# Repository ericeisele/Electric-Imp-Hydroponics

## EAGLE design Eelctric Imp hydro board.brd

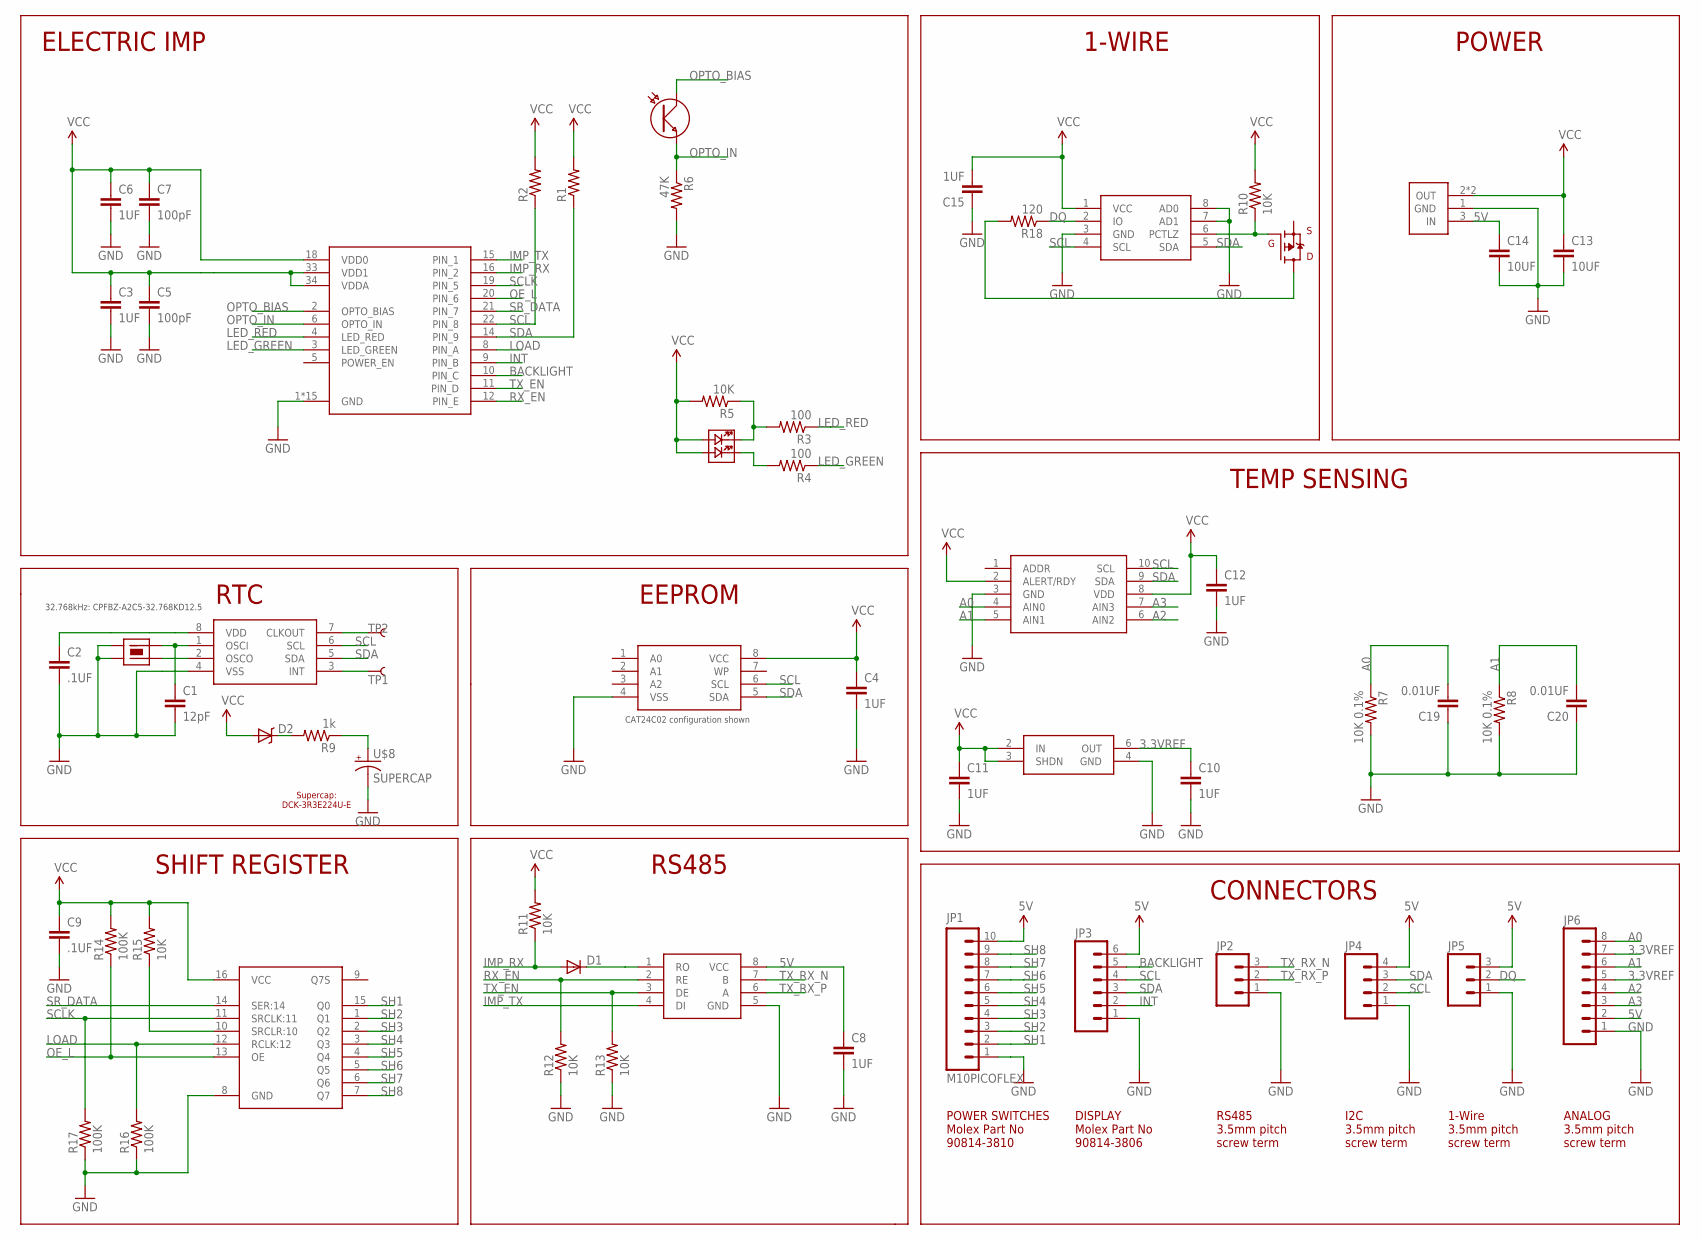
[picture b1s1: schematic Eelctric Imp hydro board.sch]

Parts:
C1: 12pF; 0805
C2, C9: .1UF; 0805
C3, C4, C6, C8, C10, C11, C12, C15: 1UF; 0805
C5, C7: 100pF; 0805
C13, C14: 10UF; 0805
C19, C20: 0.01UF; 0805
D1: DIODESOD; SOD-323
D2: DIODE-SCHOTTKY_; SMA-DIODE
JP1: M10PICOFLEX; CONNECTOR_MOLEX_PICOFLEX_10
JP2, JP5: M03SCREW_LOCK; SCREWTERMINAL-3.5MM-3_LOCK.007S
JP3: M06PICOFLEX; CONNECTOR_MOLEX_PICOFLEX_6
JP4: M04SCREW_LOCK; SCREWTERMINAL-3.5MM-4_LOCK
JP6: M083.5MM-8; SCREWTERMINAL-3.5MM-8
R1, R2: RESISTOR0805-RES; 0805
R3, R4: 100; 0805
R5, R10, R11, R12, R13, R15: 10K; 0805
R6: 47K; 0805
R7, R8: 10K 0.1%; 0805
R9: 1k; 0805
R14, R16, R17: 100K; 0805
R18: 120; 0805
TP1, TP2: TEST-POINT3; PAD.03X.03
U$1: RTC_PCF8563; SOIC8
U$2: CRYSTAL_4PIN232.768KHZ_ABS25; CRYSTAL_ABS25
U$3: EEPROM_CAT24CXX; SOIC8
U$4: RF_MODULE_IMP002
U$5: LED_BI_COLOR_4PIN; LED_LITEON_BICOLOR_TOP
U$6: PHOTOTRANSISTOR0805; 0805POL
U$8: SUPERCAP; SUPERCAP_ELENA_DCK_3R3E224U-E
U$9: DS2482-100; SO08
U$10: SHIFT_NXP_74HC595; SO-16
U$11: V_REG_LDO_3SOT-223-4_TI_TLV1117LV; SOT223
U$12: TRANSCEIVER_ST485; SOIC8
U$13: ADC_ADS1115; MSOP10
U$15: VREF_LT1461; SOIC8
U$16: MOSFET-P-CHANNELBSS84; SOT23

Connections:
3.3VREF: C10.1, JP6.5, JP6.7, U$15.6 (OUT)
5V: C8.1, C14.1, JP1.10, JP3.6, JP4.4, JP5.3, JP6.2, U$11.3 (IN), U$12.8 (VCC)
A0: C19.2, JP6.8, R7.1, U$13.4 (AIN0)
A1: C20.2, JP6.6, R8.1, U$13.5 (AIN1)
A2: JP6.4, U$13.6 (AIN2)
A3: JP6.3, U$13.7 (AIN3)
BACKLIGHT: JP3.5, U$4.10 (PIN_C)
DQ: JP5.2, R18.1, U$9.2 (IO)
GND: C1.2, C2.2, C3.2, C4.2, C5.2, C6.2, C7.2, C8.2, C9.2, C10.2, C11.2, C12.2, C13.2, C14.2, C15.1, C19.1, C20.1, JP1.1, JP2.1, JP3.1, JP4.1, JP5.1, JP6.1, R6.2, R7.2, R8.2, R12.1, R13.1, R16.1, R17.1, U$1.4 (VSS), U$2.2 (CASE2), U$2.3 (CASE1), U$3.4 (VSS), U$4.1 (GND), U$4.7 (GND), U$4.13 (GND), U$4.17 (GND), U$4.23 (GND), U$4.24 (GND), U$4.25 (GND), U$4.26 (GND), U$4.27 (GND), U$4.28 (GND), U$4.29 (GND), U$4.30 (GND), U$4.31 (GND), U$4.32 (GND), U$4.35 (GND), U$8.-, U$9.3 (GND), U$9.7 (AD1), U$9.8 (AD0), U$10.8 (GND), U$11.1 (GND), U$12.5 (GND), U$13.3 (GND), U$15.4 (GND)
IMP_RX: D1.2 (A), R11.1, U$4.16 (PIN_2)
IMP_TX: U$4.15 (PIN_1), U$12.4 (DI)
INT: JP3.2, U$4.9 (PIN_B)
LED_GREEN: R4.1, U$4.3 (LED_GREEN)
LED_RED: R3.1, U$4.4 (LED_RED)
LOAD: R16.2, U$4.8 (PIN_A), U$10.12 (RCLK:12)
unnamed: R18.2, U$16.3 (D)
unnamed: C1.1, U$1.1 (OSCI), U$2.1
unnamed: U$1.2 (OSCO), U$2.4
unnamed: TP1.P$1, U$1.3 (INT)
unnamed: TP2.P$1, U$1.7 (CLKOUT)
unnamed: D2.C, R9.2
unnamed: R3.2, R5.1, U$5.LONG-
unnamed: R15.1, U$10.10 (SRCLR:10)
unnamed: R4.2, U$5.SHORT-
unnamed: R10.1, U$9.6 (PCTLZ), U$16.1 (G)
OE_L: R14.1, U$4.20 (PIN_6), U$10.13 (OE)
OPTO_BIAS: U$4.2 (OPTO_BIAS), U$6.1(MARKING) (COLLECTOR)
OPTO_IN: R6.1, U$4.6 (OPTO_IN), U$6.2 (EMITTER)
RO: D1.1 (C), U$12.1 (RO)
RX_EN: R12.2, U$4.12 (PIN_E), U$12.2 (RE)
SCL: JP3.4, JP4.2, R2.1, U$1.6 (SCL), U$3.6 (SCL), U$4.22 (PIN_8), U$9.4 (SCL), U$13.10 (SCL)
SCLK: R17.2, U$4.19 (PIN_5), U$10.11 (SRCLK:11)
SDA: JP3.3, JP4.3, R1.1, U$1.5 (SDA), U$3.5 (SDA), U$4.14 (PIN_9), U$9.5 (SDA), U$13.9 (SDA)
SH1: JP1.2, U$10.15 (Q0)
SH2: JP1.3, U$10.1 (Q1)
SH3: JP1.4, U$10.2 (Q2)
SH4: JP1.5, U$10.3 (Q3)
SH5: JP1.6, U$10.4 (Q4)
SH6: JP1.7, U$10.5 (Q5)
SH7: JP1.8, U$10.6 (Q6)
SH8: JP1.9, U$10.7 (Q7)
SR_DATA: U$4.21 (PIN_7), U$10.14 (SER:14)
TX_EN: R13.2, U$4.11 (PIN_D), U$12.3 (DE)
TX_RX_N: JP2.3, U$12.7 (B)
TX_RX_P: JP2.2, U$12.6 (A)
VCC: C3.1, C4.1, C5.1, C6.1, C7.1, C9.1, C11.1, C12.1, C13.1, C15.2, D2.A, R1.2, R2.2, R5.2, R10.2, R11.2, R14.2, R15.2, U$3.8 (VCC), U$4.18 (VDD0), U$4.33 (VDD1), U$4.34 (VDDA), U$5.LONG+, U$5.SHORT+, U$9.1 (VCC), U$10.16 (VCC), U$11.2 (OUT), U$11.4 (OUT), U$13.2 (ALERT/RDY), U$13.8 (VDD), U$15.2 (IN), U$15.3 (SHDN)
VCLK: C2.1, R9.1, U$1.8 (VDD), U$8.+

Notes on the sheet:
RTC
EEPROM
TEMP SENSING
32.768kHz: CPFBZ-A2C5-32.768KD12.5
ELECTRIC IMP
Supercap: DCK-3R3E224U-E
RS485
SHIFT REGISTER
CONNECTORS
POWER SWITCHES Molex Part No 90814-3810
DISPLAY Molex Part No 90814-3806
RS485 3.5mm pitch screw term
I2C 3.5mm pitch screw term
1-Wire 3.5mm pitch screw term
ANALOG 3.5mm pitch screw term
1-WIRE
POWER

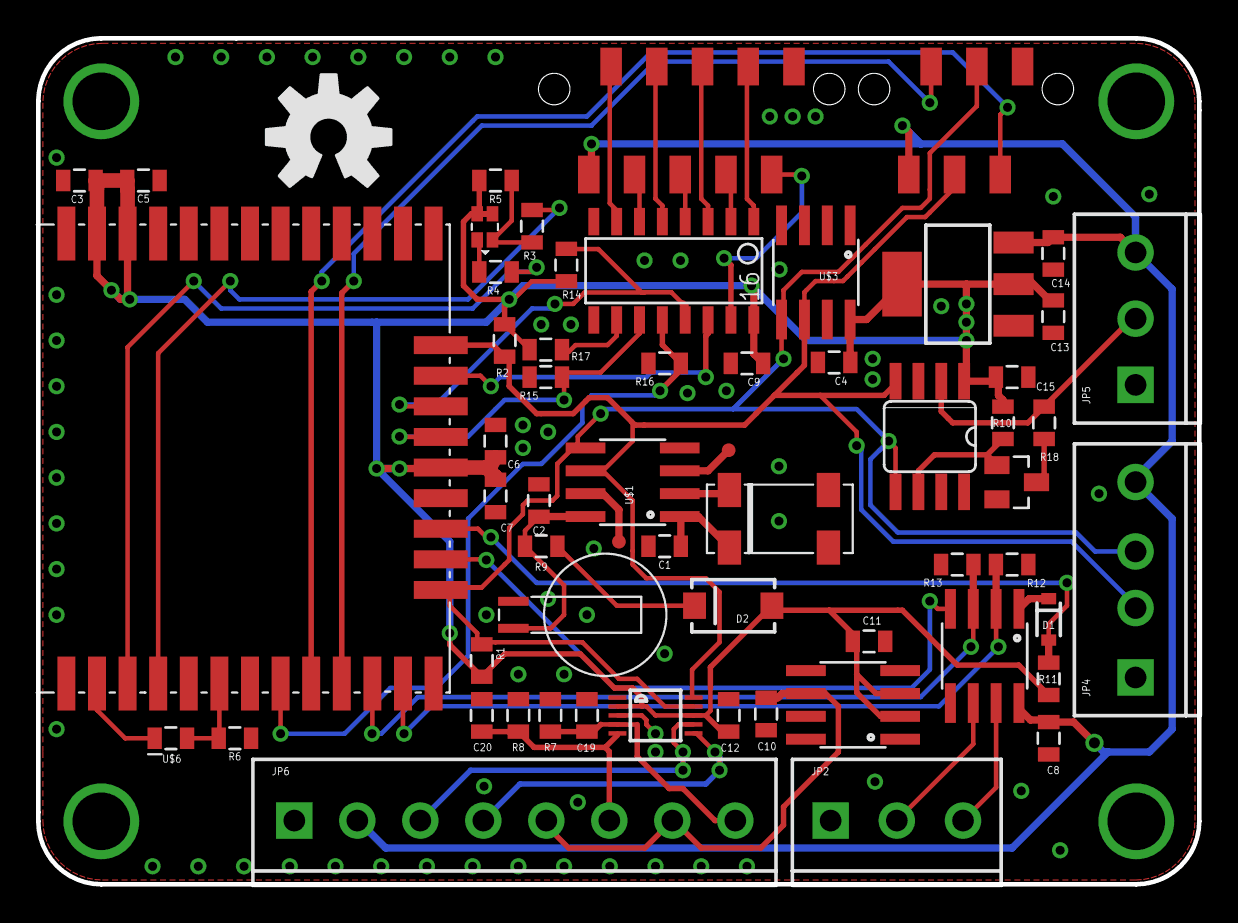
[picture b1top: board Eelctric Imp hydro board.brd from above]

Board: 2 copper layers, 64.5 x 47.0 mm, 60 parts (0 on the bottom side), 47 nets.

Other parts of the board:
U$7: OSHW-LOGO-L

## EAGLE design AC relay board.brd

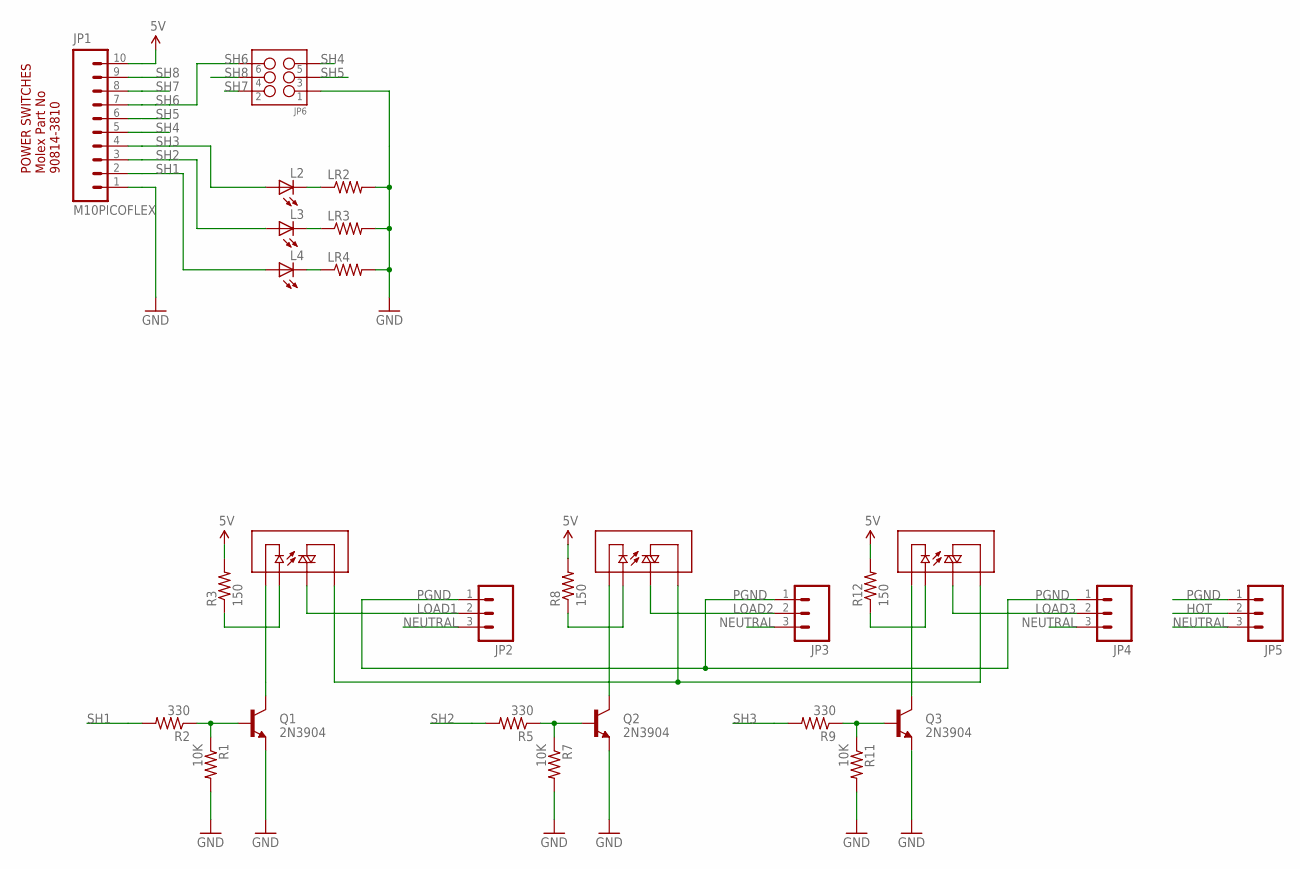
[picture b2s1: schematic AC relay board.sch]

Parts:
JP1: M10PICOFLEX; CONNECTOR_MOLEX_PICOFLEX_10
JP2, JP3, JP4, JP5: M03SCREW_LOCK; SCREWTERMINAL-3.5MM-3_LOCK.007S
JP6: M03X2NO_SILK; 2X3-NS
L2, L3, L4: LED0805; LED-0805
LR2, LR3, LR4: RESISTOR0805-RES; 0805
Q1, Q2, Q3: 2N3904; SOT23
R1, R7, R11: 10K; 0805
R2, R5, R9: 330; 0805
R3, R8, R12: 150; 0805
U1, U2, U3: S108T02; RELAY-S202S01F

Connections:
5V: JP1.10, R3.2, R8.2, R12.2
COIL: Q1.3 (C), U1.4 (-)
COIL1: Q2.3 (C), U2.4 (-)
COIL2: Q3.3 (C), U3.4 (-)
GND: JP1.1, JP6.1, LR2.2, LR3.2, LR4.2, Q1.2 (E), Q2.2 (E), Q3.2 (E), R1.2, R7.2, R11.2
HOT: JP5.2, U1.2 (T1), U2.2 (T1), U3.2 (T1)
LOAD1: JP2.2, U1.1 (T2)
LOAD2: JP3.2, U2.1 (T2)
LOAD3: JP4.2, U3.1 (T2)
unnamed: R3.1, U1.3 (+)
unnamed: Q2.1 (B), R5.1, R7.1
unnamed: L4.C- (C), LR4.1
unnamed: R8.1, U2.3 (+)
unnamed: Q3.1 (B), R9.1, R11.1
unnamed: Q1.1 (B), R1.1, R2.1
unnamed: L3.C- (C), LR3.1
unnamed: R12.1, U3.3 (+)
unnamed: L2.C- (C), LR2.1
NEUTRAL: JP2.3, JP3.3, JP4.3, JP5.3
PGND: JP2.1, JP3.1, JP4.1, JP5.1
SH1: JP1.2, L4.A+ (A), R2.2
SH2: JP1.3, L3.A+ (A), R5.2
SH3: JP1.4, L2.A+ (A), R9.2
SH4: JP1.5, JP6.5
SH5: JP1.6, JP6.3
SH6: JP1.7, JP6.6
SH7: JP1.8, JP6.2
SH8: JP1.9, JP6.4

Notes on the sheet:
POWER SWITCHES Molex Part No 90814-3810

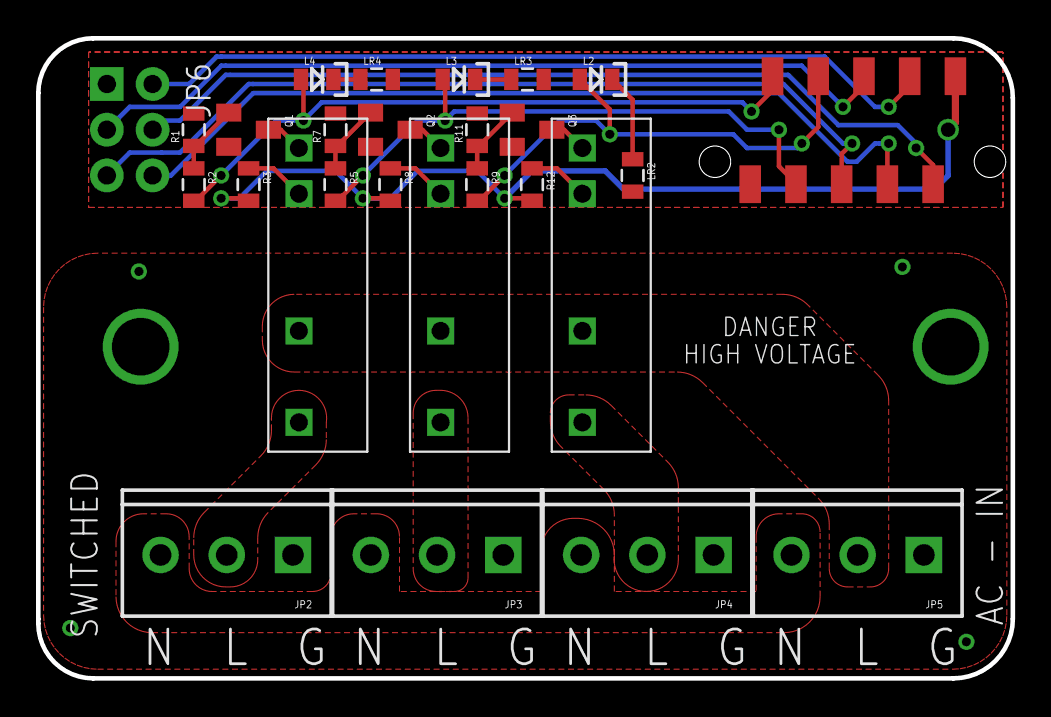
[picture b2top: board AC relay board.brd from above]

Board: 2 copper layers, 54.1 x 35.6 mm, 27 parts (0 on the bottom side), 28 nets.

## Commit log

2015-11-30 :octocat: Added .gitattributes & .gitignore files
2015-11-30 Initial commit of Hydroponic controller

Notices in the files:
parts and their libraries:
11.SparkFun: Licensing: CC v3.0 Share-Alike You are welcome to use this library for commercial purposes.
SparkFun-Aesthetics: Licensing: Creative Commons ShareAlike 4.0 International - https://creativecommons.org/licenses/by-sa/4.0
